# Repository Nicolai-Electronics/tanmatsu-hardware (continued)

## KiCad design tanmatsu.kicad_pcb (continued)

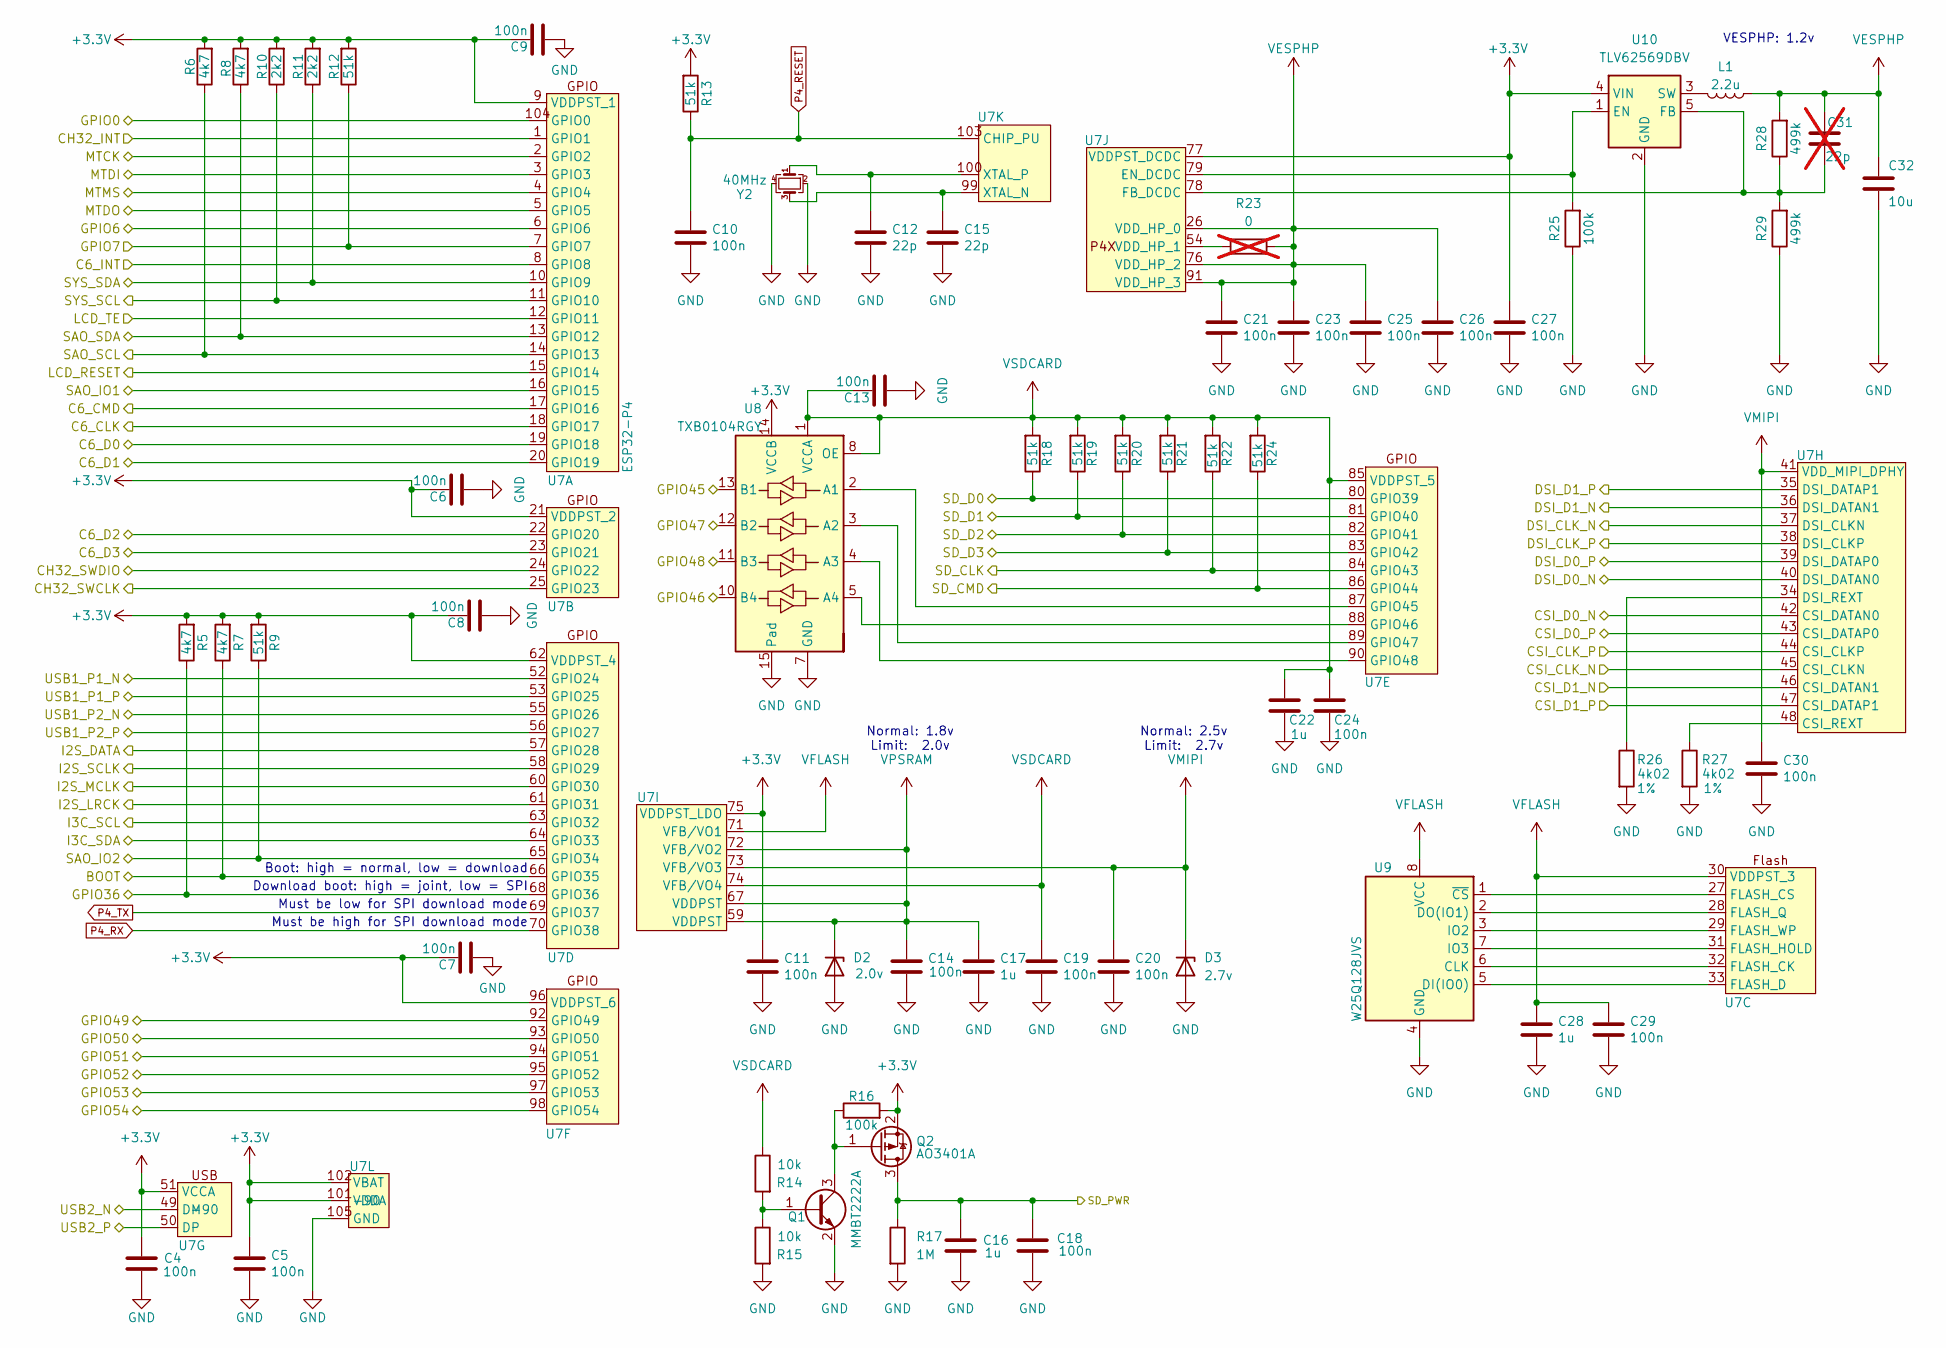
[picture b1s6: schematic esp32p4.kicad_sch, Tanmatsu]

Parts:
C4, C5, C6, C7, C8, C9, C10, C11, C13, C14, C18, C19, C20, C21, C23, C24, C25, C26, C27, C29, C30: 100n; C_0402_1005Metric; LCSC C307331
C12, C15: 22p; C_0402_1005Metric; LCSC C1555
C16, C17, C22, C28: 1u; C_0603_1608Metric; LCSC C5199872
C31: 22p; C_0402_1005Metric; LCSC C1555; not fitted
C32: 10u; C_0805_2012Metric; LCSC C3039694
D2: 2.0v; D_SOD-123; LCSC C438287
D3: 2.7v; D_SOD-323F; LCSC C550976
L1: 2.2u; Inductor_MSC20FC; LCSC C48945436
Q1: MMBT2222A; SOT-23; LCSC C8512
Q2: AO3401A; SOT-23; LCSC C15127
R5, R6, R7, R8: 4k7; R_0402_1005Metric; LCSC C25900
R9, R12, R13, R18, R19, R20, R21, R22, R24: 51k; R_0402_1005Metric; LCSC C25794
R10, R11: 2k2; R_0402_1005Metric; LCSC C25879
R14, R15: 10k; R_0402_1005Metric; LCSC C60490
R16, R25: 100k; R_0402_1005Metric; LCSC C25741
R17: 1M; R_0402_1005Metric; LCSC C26083
R23: 0; R_0402_1005Metric; LCSC C2906877; not fitted
R26, R27: 4k02; R_0402_1005Metric; LCSC C43251
R28, R29: 499k; R_0402_1005Metric; LCSC C137971
U7: ESP32-P4; QFN-104_EP_10x10_Pitch0.35mm-ESP32-P4; LCSC C22387510
U8: TXB0104RGY; Texas_S-PVQFN-N14; LCSC C400708
U9: W25Q128JVS; SOIC-8_5.23x5.23mm_P1.27mm; LCSC C97521
U10: TLV62569DBV; SOT-23-5; LCSC C141836
Y2: 40MHz; Crystal_SMD_3225-4Pin_3.2x2.5mm; LCSC C2901712

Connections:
+3.3V: C4.1, C5.1, C6.1, C7.1, C8.1, C9.1, C11.1, C27.1, Q2.2 (S), R5.2, R6.2, R7.2, R8.2, R9.2, R10.2, R11.2, R12.2, R13.2, R16.2, U7.9 (VDDPST_1), U7.21 (VDDPST_2), U7.51 (VCCA), U7.62 (VDDPST_4), U7.75 (VDDPST_LDO), U7.77 (VDDPST_DCDC), U7.96 (VDDPST_6), U7.101 (VDDA), U7.102 (VBAT), U8.14 (VCCB), U10.4 (VIN); also elsewhere on the board
/Application processor/C6_CLK: U7.18 (GPIO17); also elsewhere on the board
/Application processor/C6_CMD: U7.17 (GPIO16); also elsewhere on the board
/Application processor/C6_D0: U7.19 (GPIO18); also elsewhere on the board
/Application processor/C6_D1: U7.20 (GPIO19); also elsewhere on the board
/Application processor/C6_D2: U7.22 (GPIO20); also elsewhere on the board
/Application processor/C6_D3: U7.23 (GPIO21); also elsewhere on the board
/Application processor/C6_INT: U7.8 (GPIO8); also elsewhere on the board
/Application processor/CH32_INT: U7.1 (GPIO1); also elsewhere on the board
/Application processor/CH32_SWCLK: U7.25 (GPIO23); also elsewhere on the board
/Application processor/CH32_SWDIO: U7.24 (GPIO22); also elsewhere on the board
/Application processor/CSI_CLK_N: U7.45 (CSI_CLKN); also elsewhere on the board
/Application processor/CSI_CLK_P: U7.44 (CSI_CLKP); also elsewhere on the board
/Application processor/CSI_D0_N: U7.42 (CSI_DATAN0); also elsewhere on the board
/Application processor/CSI_D0_P: U7.43 (CSI_DATAP0); also elsewhere on the board
/Application processor/CSI_D1_N: U7.46 (CSI_DATAN1); also elsewhere on the board
/Application processor/CSI_D1_P: U7.47 (CSI_DATAP1); also elsewhere on the board
/Application processor/LCD_RESET: U7.15 (GPIO14); also elsewhere on the board
/Application processor/LCD_TE: U7.12 (GPIO11); also elsewhere on the board
/Application processor/SD_CLK: R22.1, U7.84 (GPIO43); also elsewhere on the board
/Application processor/SD_CMD: R24.1, U7.86 (GPIO44); also elsewhere on the board
/Application processor/SD_D0: R18.1, U7.80 (GPIO39); also elsewhere on the board
/Application processor/SD_D1: R19.1, U7.81 (GPIO40); also elsewhere on the board
/Application processor/SD_D2: R20.1, U7.82 (GPIO41); also elsewhere on the board
/Application processor/SD_D3: R21.1, U7.83 (GPIO42); also elsewhere on the board
/Application processor/SD_PWR: C16.1, C18.1, Q2.3 (D), R17.1; also elsewhere on the board
/Application processor/USB1_P1_N: U7.52 (GPIO24); also elsewhere on the board
/Application processor/USB1_P1_P: U7.53 (GPIO25); also elsewhere on the board
/Application processor/USB2_N: U7.49 (DM); also elsewhere on the board
/Application processor/USB2_P: U7.50 (DP); also elsewhere on the board
/DSI_CLK_N: U7.37 (DSI_CLKN); also elsewhere on the board
/DSI_CLK_P: U7.38 (DSI_CLKP); also elsewhere on the board
/DSI_D0_N: U7.40 (DSI_DATAN0); also elsewhere on the board
/DSI_D0_P: U7.39 (DSI_DATAP0); also elsewhere on the board
/DSI_D1_N: U7.36 (DSI_DATAN1); also elsewhere on the board
/DSI_D1_P: U7.35 (DSI_DATAP1); also elsewhere on the board
BOOT: R7.1, U7.66 (GPIO35); also elsewhere on the board
E0: R5.1, U7.68 (GPIO36); also elsewhere on the board
E1: U7.104 (GPIO0); also elsewhere on the board
E2: U7.6 (GPIO6); also elsewhere on the board
E3: U8.10 (B4); also elsewhere on the board
E4: U8.12 (B2); also elsewhere on the board
E5: U8.11 (B3); also elsewhere on the board
E6: U8.13 (B1); also elsewhere on the board
E7: R12.1, U7.7 (GPIO7); also elsewhere on the board
E8: U7.98 (GPIO54); also elsewhere on the board
E9: U7.92 (GPIO49); also elsewhere on the board
E10: U7.97 (GPIO53); also elsewhere on the board
E11: U7.95 (GPIO52); also elsewhere on the board
E12: U7.94 (GPIO51); also elsewhere on the board
E13: U7.93 (GPIO50); also elsewhere on the board
EXT_USB_N: U7.55 (GPIO26); also elsewhere on the board
EXT_USB_P: U7.56 (GPIO27); also elsewhere on the board
GND: C4.2, C5.2, C6.2, C7.2, C8.2, C9.2, C10.2, C11.2, C12.2, C13.2, C14.2, C15.2, C16.2, C17.2, C18.2, C19.2, C20.2, C21.2, C22.2, C23.2, C24.2, C25.2, C26.2, C27.2, C28.2, C29.2, C30.2, C32.2, D2.2 (A), D3.2 (A), Q1.2 (E), R15.2, R17.2, R25.1, R26.2, R27.2, R29.1, U7.105 (GND), U8.7 (GND), U8.15 (Pad), U9.4 (GND), U10.2 (GND), Y2.2, Y2.4; also elsewhere on the board
I2S_DATA: U7.57 (GPIO28); also elsewhere on the board
I2S_LRCK: U7.61 (GPIO31); also elsewhere on the board
I2S_MCLK: U7.60 (GPIO30); also elsewhere on the board
I2S_SCLK: U7.58 (GPIO29); also elsewhere on the board
I3C_SCL: U7.63 (GPIO32); also elsewhere on the board
I3C_SDA: U7.64 (GPIO33); also elsewhere on the board
INT_SCL: R10.1, U7.11 (GPIO10); also elsewhere on the board
INT_SDA: R11.1, U7.10 (GPIO9); also elsewhere on the board
MTCK: U7.2 (GPIO2); also elsewhere on the board
MTDI: U7.3 (GPIO3); also elsewhere on the board
MTDO: U7.5 (GPIO5); also elsewhere on the board
MTMS: U7.4 (GPIO4); also elsewhere on the board
unnamed: Q1.1 (B), R14.2, R15.1
unnamed: Q1.3 (C), Q2.1 (G), R16.1
unnamed: U7.32 (FLASH_CK), U9.6 (CLK)
unnamed: U7.27 (FLASH_CS), U9.1 (~CS)
unnamed: U7.33 (FLASH_D), U9.5 (DI(IO0))
unnamed: U7.31 (FLASH_HOLD), U9.7 (IO3)
unnamed: U7.28 (FLASH_Q), U9.2 (DO(IO1))
unnamed: U7.29 (FLASH_WP), U9.3 (IO2)
unnamed: U7.87 (GPIO45), U8.2 (A1)
unnamed: U7.88 (GPIO46), U8.5 (A4)
unnamed: U7.89 (GPIO47), U8.3 (A2)
unnamed: U7.90 (GPIO48), U8.4 (A3)
unnamed: R27.1, U7.48 (CSI_REXT)
unnamed: R26.1, U7.34 (DSI_REXT)
unnamed: R23.2, U7.54 (VDD_HP_1)
unnamed: C15.1, U7.99 (XTAL_N), Y2.3
unnamed: C12.1, U7.100 (XTAL_P), Y2.1
unnamed: R25.2, U7.79 (EN_DCDC), U10.1 (EN)
unnamed: C31.2, R28.1, R29.2, U7.78 (FB_DCDC), U10.5 (FB)
unnamed: L1.2, U10.3 (SW)
P4_RESET: C10.1, R13.1, U7.103 (CHIP_PU); also elsewhere on the board
P4_RX: U7.70 (GPIO38); also elsewhere on the board
P4_TX: U7.69 (GPIO37); also elsewhere on the board
SAO_IO1: U7.16 (GPIO15); also elsewhere on the board
SAO_IO2: R9.1, U7.65 (GPIO34); also elsewhere on the board
SAO_SCL: R6.1, U7.14 (GPIO13); also elsewhere on the board
SAO_SDA: R8.1, U7.13 (GPIO12); also elsewhere on the board
VESPHP: C21.1, C23.1, C25.1, C26.1, C31.1, C32.1, L1.1, R23.1, R28.2, U7.26 (VDD_HP_0), U7.76 (VDD_HP_2), U7.91 (VDD_HP_3)
VFLASH: C28.1, C29.1, U7.30 (VDDPST_3), U7.71 (VFB/VO1), U9.8 (VCC)
VMIPI: C20.1, C30.1, D3.1 (K), U7.41 (VDD_MIPI_DPHY), U7.73 (VFB/VO3)
VPSRAM: C14.1, C17.1, D2.1 (K), U7.59 (VDDPST), U7.67 (VDDPST), U7.72 (VFB/VO2)
VSDCARD: C13.1, C19.1, C22.1, C24.1, R14.1, R18.2, R19.2, R20.2, R21.2, R22.2, R24.2, U7.74 (VFB/VO4), U7.85 (VDDPST_5), U8.1 (VCCA), U8.8 (OE)

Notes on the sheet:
Normal: 1.8v Limit: 2.0v
Boot: high = normal, low = download
Must be high for SPI download mode
Normal: 2.5v Limit: 2.7v
Must be low for SPI download mode
Download boot: high = joint, low = SPI
VESPHP: 1.2v

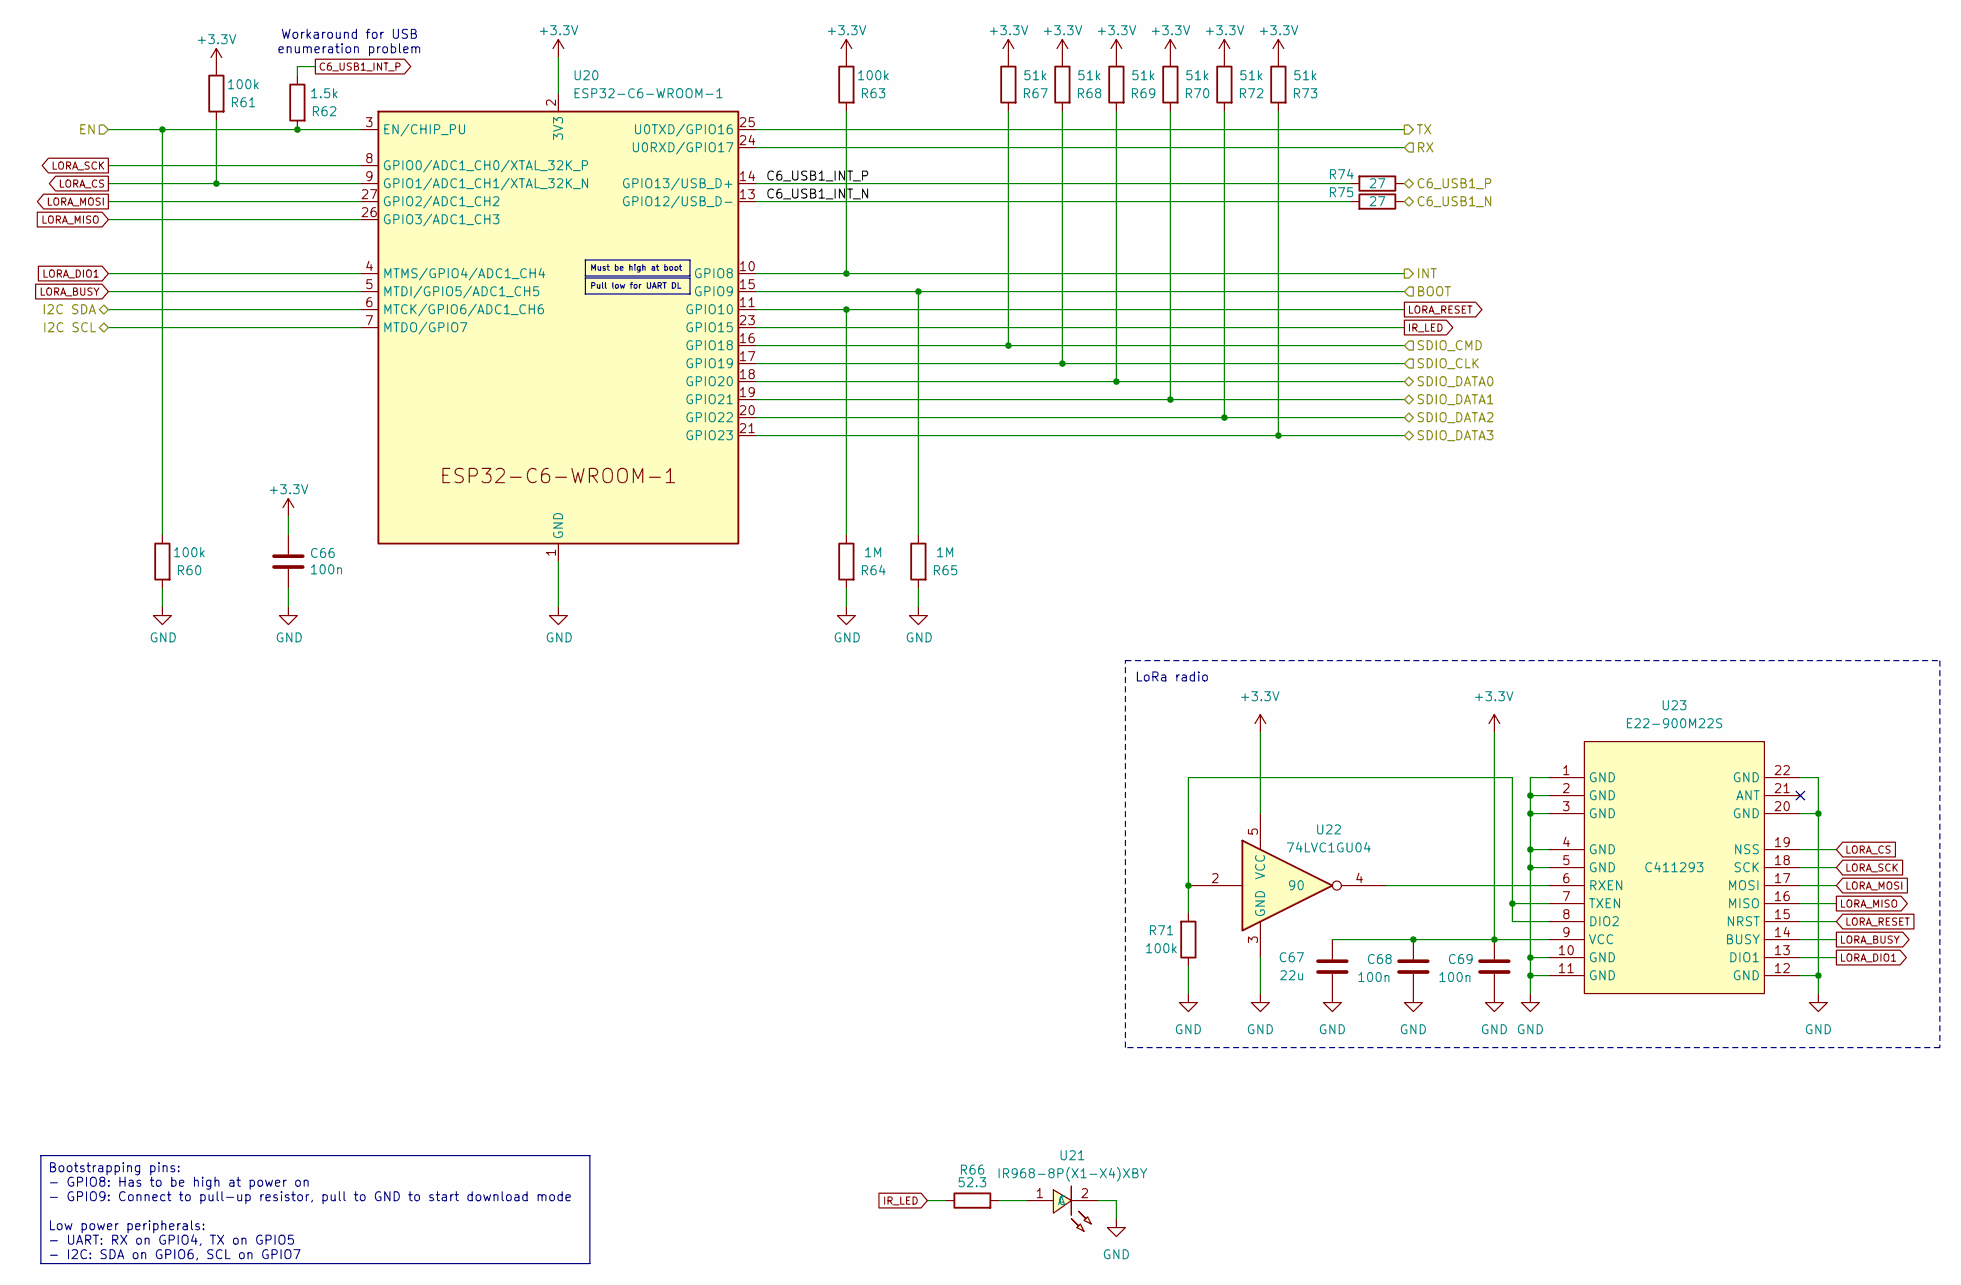
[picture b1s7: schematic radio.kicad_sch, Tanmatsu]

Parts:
C66, C68, C69: 100n; C_0402_1005Metric; LCSC C307331
C67: 22u; C_0805_2012Metric; LCSC C602037
R60, R61, R63, R71: 100k; R_0402_1005Metric; LCSC C25741
R62: 1.5k; R_0402_1005Metric; LCSC C25867
R64, R65: 1M; R_0402_1005Metric; LCSC C26083
R66: 52.3; R_0402_1005Metric; LCSC C114978
R67, R68, R69, R70, R72, R73: 51k; R_0402_1005Metric; LCSC C25794
R74, R75: 27; R_0402_1005Metric; LCSC C25100
U20: ESP32-C6-WROOM-1; LCSC C5366877
U21: IR968-8P(X1-X4)XBY; LED-TH_L3.0-W2.9-P2.54-FD; LCSC C47416529
U22: 74LVC1GU04; SOT-353_SC-70-5; LCSC C485082
U23: E22-900M22S; WIRELM-SMD_E22-900M22S; LCSC C411293

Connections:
+3.3V: C66.1, C67.1, C68.1, C69.1, R61.1, R63.1, R67.1, R68.1, R69.1, R70.1, R72.1, R73.1, U20.2 (3V3), U22.5 (VCC), U23.9 (VCC); also elsewhere on the board
/Application processor/C6_CLK: R68.2, U20.17 (GPIO19); also elsewhere on the board
/Application processor/C6_CMD: R67.2, U20.16 (GPIO18); also elsewhere on the board
/Application processor/C6_D0: R69.2, U20.18 (GPIO20); also elsewhere on the board
/Application processor/C6_D1: R70.2, U20.19 (GPIO21); also elsewhere on the board
/Application processor/C6_D2: R72.2, U20.20 (GPIO22); also elsewhere on the board
/Application processor/C6_D3: R73.2, U20.21 (GPIO23); also elsewhere on the board
/Application processor/C6_INT: R63.2, U20.10 (GPIO8); also elsewhere on the board
/Coprocessor/RADIO_BOOT: R65.1, U20.15 (GPIO9); also elsewhere on the board
/Radio/C6_USB1_INT_N: R75.2, U20.13 (GPIO12/USB_D-)
/Radio/C6_USB1_N: R75.1; also elsewhere on the board
/Radio/C6_USB1_P: R74.1; also elsewhere on the board
/Radio/TX: U20.25 (U0TXD/GPIO16); also elsewhere on the board
C6_USB1_INT_P: R62.1, R74.2, U20.14 (GPIO13/USB_D+)
CAM_IO0: R60.1, R62.2, U20.3 (EN/CHIP_PU); also elsewhere on the board
E10: U20.24 (U0RXD/GPIO17); also elsewhere on the board
GND: C66.2, C67.2, C68.2, C69.2, R60.2, R64.2, R65.2, R71.1, U20.1 (GND), U20.12 (GPIO11), U20.28 (GND), U20.29 (GND), U21.2 (C), U22.3 (GND), U23.1 (GND), U23.2 (GND), U23.3 (GND), U23.4 (GND), U23.5 (GND), U23.10 (GND), U23.11 (GND), U23.12 (GND), U23.20 (GND), U23.22 (GND); also elsewhere on the board
INT_SCL: U20.7 (MTDO/GPIO7); also elsewhere on the board
INT_SDA: U20.6 (MTCK/GPIO6/ADC1_CH6); also elsewhere on the board
IR_LED: R66.1, U20.23 (GPIO15)
LORA_BUSY: U20.5 (MTDI/GPIO5/ADC1_CH5), U23.14 (BUSY)
LORA_CS: R61.2, U20.9 (GPIO1/ADC1_CH1/XTAL_32K_N), U23.19 (NSS)
LORA_DIO1: U20.4 (MTMS/GPIO4/ADC1_CH4), U23.13 (DIO1)
LORA_MISO: U20.26 (GPIO3/ADC1_CH3), U23.16 (MISO)
LORA_MOSI: U20.27 (GPIO2/ADC1_CH2), U23.17 (MOSI)
LORA_RESET: R64.1, U20.11 (GPIO10), U23.15 (NRST)
LORA_SCK: U20.8 (GPIO0/ADC1_CH0/XTAL_32K_P), U23.18 (SCK)
unnamed: R66.2, U21.1 (A)
unnamed: R71.2, U22.2, U23.7 (TXEN), U23.8 (DIO2)
unnamed: U22.4, U23.6 (RXEN)

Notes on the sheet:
LoRa radio
Workaround for USB enumeration problem
Pull low for UART DL
Must be high at boot
Bootstrapping pins: - GPIO8: Has to be high at power on - GPIO9: Connect to pull-up resistor, pull to GND to start download mode Low power peripherals: - UART: RX on GPIO4, TX on GPIO5 - I2C: SDA on GPIO6, SCL on GPIO7

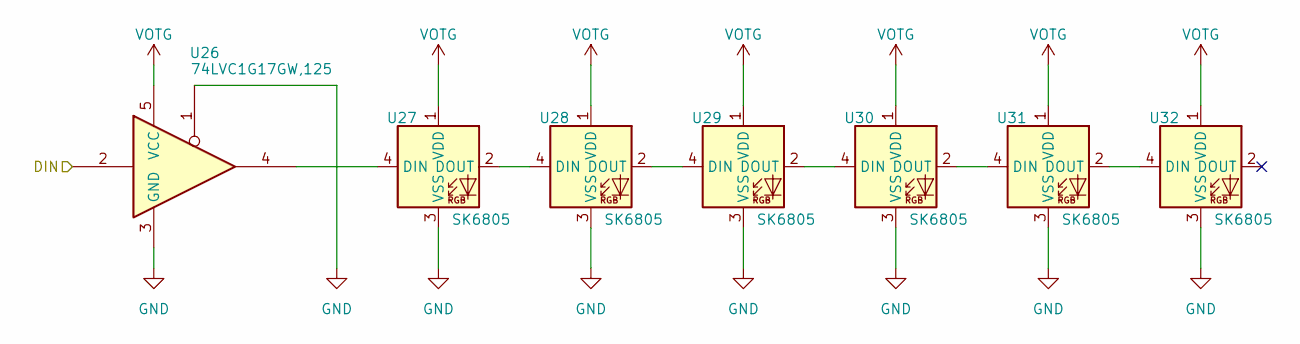
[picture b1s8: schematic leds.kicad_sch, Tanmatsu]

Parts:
U26: 74LVC1G17GW,125; SOT-353_SC-70-5; LCSC C426705
U27, U28, U29, U30, U31, U32: SK6805; SK6805-EC20; LCSC C2890036

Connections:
/Coprocessor/LED_DATA: U26.2; also elsewhere on the board
GND: U26.1, U26.3 (GND), U27.3 (VSS), U28.3 (VSS), U29.3 (VSS), U30.3 (VSS), U31.3 (VSS), U32.3 (VSS); also elsewhere on the board
unnamed: U26.4, U27.4 (DIN)
unnamed: U27.2 (DOUT), U28.4 (DIN)
unnamed: U28.2 (DOUT), U29.4 (DIN)
unnamed: U29.2 (DOUT), U30.4 (DIN)
unnamed: U30.2 (DOUT), U31.4 (DIN)
unnamed: U31.2 (DOUT), U32.4 (DIN)
VOTG: U26.5 (VCC), U27.1 (VDD), U28.1 (VDD), U29.1 (VDD), U30.1 (VDD), U31.1 (VDD), U32.1 (VDD); also elsewhere on the board

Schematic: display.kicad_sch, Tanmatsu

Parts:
C83, C84, C85, C86: 10n; C_0402_1005Metric; LCSC C15195
CN1: Display; tanmatsu_display; LCSC C3036280
R86: 51k; R_0402_1005Metric; LCSC C25794
R87: 100k; R_0402_1005Metric; LCSC C25741

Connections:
+3.3V: C83.1, C84.1, C85.1, C86.1, CN1.23 (VCI), CN1.24 (IOVCC), R86.1; also elsewhere on the board
+BL-LCD: CN1.2 (LCM_LEDA); also elsewhere on the board
-BL-LCD: CN1.1 (LCM_LEDK); also elsewhere on the board
/Application processor/LCD_RESET: CN1.21 (LCM_RST), R86.2; also elsewhere on the board
/Application processor/LCD_TE: CN1.20 (DSI_TE), R87.1; also elsewhere on the board
/DSI_CLK_N: CN1.8 (TCN); also elsewhere on the board
/DSI_CLK_P: CN1.7 (TCP); also elsewhere on the board
/DSI_D0_N: CN1.5 (TDN0); also elsewhere on the board
/DSI_D0_P: CN1.4 (TDP0); also elsewhere on the board
/DSI_D1_N: CN1.11 (TDN1); also elsewhere on the board
/DSI_D1_P: CN1.10 (TDP1); also elsewhere on the board
GND: C83.2, C84.2, C85.2, C86.2, CN1.3 (GND), CN1.6 (GND), CN1.9 (GND), CN1.12 (GND), CN1.13 (TP-SCL), CN1.14 (TP-SDA), CN1.15 (TP-RST), CN1.16 (TP-INT), CN1.17 (TP-VDD), CN1.18 (GND), CN1.19 (GND), CN1.22 (GND), CN1.25, CN1.26, R87.2; also elsewhere on the board

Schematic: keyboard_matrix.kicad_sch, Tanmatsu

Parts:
D4, D5, D6, D7, D14, D15, D16, D17: LTW-010DCG-SR-G; LCSC C5175309
D8, D9, D10, D11, D12, D13, D18, D19, D20, D21, D22, D23, D24, D25, D26, D27, D28, D29, D30, D31, D32, D33, D34, D35, D36, D37, D38, D39, D40, D41, D42, D43, D44, D45, D46, D47, D48, D49, D50, D51, D52, D53, D54, D55, D56, D57, D58, D59, D60, D61, D62, D63, D64, D65, D66, D67, D68, D69, D70, D71, D72, D73, D74, D75, D76, D77, D78, D79, D80, D81, D82, D83: 1N4148WS; D_SOD-323; LCSC C2843305
Q3: AP2302B; SOT-23; LCSC C406812
R37: 100k; R_0402_1005Metric; LCSC C25741
R38: 4k7; R_0402_1005Metric; LCSC C25900
R39, R40, R41, R42, R43, R44, R45, R46: 10k; R_0402_1005Metric; LCSC C60490
U13: Keyboard; keyboard_arturo182

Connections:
+BL-KB: D4.2 (A), D14.2 (A); also elsewhere on the board
-BL-KB: D7.1 (K), D17.1 (K); also elsewhere on the board
/Coprocessor/Keyboard/EXT: R37.2, R38.1; also elsewhere on the board
GND: R37.1, R39.2, R40.2, R41.2, R42.2, R43.2, R44.2, R45.2, R46.2; also elsewhere on the board
KB_COL0: D8.1 (K), D10.1 (K), D12.1 (K), D36.1 (K), D38.1 (K), D56.1 (K), D60.1 (K), D62.1 (K), D64.1 (K), R39.1; also elsewhere on the board
KB_COL1: D18.1 (K), D20.1 (K), D22.1 (K), D40.1 (K), D42.1 (K), D57.1 (K), D66.1 (K), D68.1 (K), D70.1 (K), R40.1; also elsewhere on the board
KB_COL2: D24.1 (K), D26.1 (K), D28.1 (K), D45.1 (K), D47.1 (K), D58.1 (K), D72.1 (K), D74.1 (K), D76.1 (K), R41.1; also elsewhere on the board
KB_COL3: D30.1 (K), D32.1 (K), D34.1 (K), D50.1 (K), D52.1 (K), D59.1 (K), D78.1 (K), D80.1 (K), D82.1 (K), R42.1; also elsewhere on the board
KB_COL4: D9.1 (K), D11.1 (K), D13.1 (K), D37.1 (K), D39.1 (K), D44.1 (K), D61.1 (K), D63.1 (K), D65.1 (K), R43.1; also elsewhere on the board
KB_COL5: D19.1 (K), D21.1 (K), D23.1 (K), D41.1 (K), D43.1 (K), D49.1 (K), D67.1 (K), D69.1 (K), D71.1 (K), R44.1; also elsewhere on the board
KB_COL6: D25.1 (K), D27.1 (K), D29.1 (K), D46.1 (K), D48.1 (K), D54.1 (K), D73.1 (K), D75.1 (K), D77.1 (K), R45.1; also elsewhere on the board
KB_COL7: D31.1 (K), D33.1 (K), D35.1 (K), D51.1 (K), D53.1 (K), D55.1 (K), D79.1 (K), D81.1 (K), D83.1 (K), R46.1; also elsewhere on the board
KB_ROW0: U13.1 (ESC), U13.3 (F1), U13.5 (F2), U13.7 (F3), U13.17 (`), U13.19 (1), U13.21 (2), U13.23 (3); also elsewhere on the board
KB_ROW1: U13.43 (TAB), U13.45 (Q), U13.47 (W), U13.49 (E), U13.69 (FN), U13.71 (A), U13.73 (S), U13.75 (D); also elsewhere on the board
KB_ROW2: U13.95 (SHL), U13.97 (Z), U13.99 (X), U13.101 (C), U13.121 (CTRL), U13.123 (MT), U13.125 (ALT), U13.127 (\); also elsewhere on the board
KB_ROW3: U13.25 (4), U13.27 (5), U13.29 (6), U13.31 (7), U13.51 (R), U13.53 (T), U13.55 (Y), U13.57 (U); also elsewhere on the board
KB_ROW4: U13.77 (F), U13.79 (G), U13.81 (H), U13.83 (J), U13.103 (V), U13.105 (B), U13.107 (N), U13.109 (M); also elsewhere on the board
KB_ROW5: U13.9 (F4), U13.11 (F5), U13.13 (F6), U13.15 (BS), U13.35 (9), U13.37 (0), U13.39 (-), U13.41 (=); also elsewhere on the board
KB_ROW6: U13.61 (O), U13.63, U13.65 ([), U13.67 (]), U13.87 (L), U13.89 (;), U13.91 ('), U13.93 (RET); also elsewhere on the board
KB_ROW7: U13.113 (.), U13.115 (/), U13.117 (/\), U13.119 (SHR), U13.135 (AGR), U13.137 (<), U13.139 (\/), U13.141 (>); also elsewhere on the board
KB_ROW8: Q3.3 (D), U13.33 (8), U13.59 (I), U13.85 (K), U13.111 (,), U13.129 (SP), U13.131 (SP), U13.133 (SP); also elsewhere on the board
unnamed: D4.1 (K), D5.2 (A)
unnamed: D5.1 (K), D6.2 (A)
unnamed: D6.1 (K), D7.2 (A)
unnamed: D8.2 (A), U13.2
unnamed: D9.2 (A), U13.18
unnamed: D10.2 (A), U13.44
unnamed: D11.2 (A), U13.70
unnamed: D12.2 (A), U13.96
unnamed: D13.2 (A), U13.122
unnamed: D14.1 (K), D15.2 (A)
unnamed: D15.1 (K), D16.2 (A)
unnamed: D16.1 (K), D17.2 (A)
unnamed: D18.2 (A), U13.4
unnamed: D19.2 (A), U13.20
unnamed: D20.2 (A), U13.46
unnamed: D21.2 (A), U13.72
unnamed: D22.2 (A), U13.98
unnamed: D23.2 (A), U13.124
unnamed: D24.2 (A), U13.6
unnamed: D25.2 (A), U13.22
unnamed: D26.2 (A), U13.48
unnamed: D27.2 (A), U13.74
unnamed: D28.2 (A), U13.100
unnamed: D29.2 (A), U13.126
unnamed: D30.2 (A), U13.8
unnamed: D31.2 (A), U13.24
unnamed: D32.2 (A), U13.50
unnamed: D33.2 (A), U13.76
unnamed: D34.2 (A), U13.102
unnamed: D35.2 (A), U13.128
unnamed: D36.2 (A), U13.26
unnamed: D37.2 (A), U13.52
unnamed: D38.2 (A), U13.78
unnamed: D39.2 (A), U13.104
unnamed: D40.2 (A), U13.28
unnamed: D41.2 (A), U13.54
unnamed: D42.2 (A), U13.80
unnamed: D43.2 (A), U13.106
unnamed: D44.2 (A), U13.130
unnamed: D45.2 (A), U13.30
unnamed: D46.2 (A), U13.56
unnamed: D47.2 (A), U13.82
unnamed: D48.2 (A), U13.108
unnamed: D49.2 (A), U13.132
unnamed: D50.2 (A), U13.32
unnamed: D51.2 (A), U13.58
unnamed: D52.2 (A), U13.84
unnamed: D53.2 (A), U13.110
unnamed: D54.2 (A), U13.134
unnamed: D55.2 (A), Q3.2 (S)
unnamed: D56.2 (A), U13.34
unnamed: D57.2 (A), U13.60
unnamed: D58.2 (A), U13.86
unnamed: D59.2 (A), U13.112
unnamed: D60.2 (A), U13.10
unnamed: D61.2 (A), U13.36
unnamed: D62.2 (A), U13.62
unnamed: D63.2 (A), U13.88
unnamed: D64.2 (A), U13.114
unnamed: D65.2 (A), U13.136
unnamed: D66.2 (A), U13.12
unnamed: D67.2 (A), U13.38
unnamed: D68.2 (A), U13.64
unnamed: D69.2 (A), U13.90
unnamed: D70.2 (A), U13.116
unnamed: D71.2 (A), U13.138
unnamed: D72.2 (A), U13.14
unnamed: D73.2 (A), U13.40
unnamed: D74.2 (A), U13.66
unnamed: D75.2 (A), U13.92
unnamed: D76.2 (A), U13.118
unnamed: D77.2 (A), U13.140
unnamed: D78.2 (A), U13.16
unnamed: D79.2 (A), U13.42
unnamed: D80.2 (A), U13.68
unnamed: D81.2 (A), U13.94
unnamed: D82.2 (A), U13.120
unnamed: D83.2 (A), U13.142
unnamed: Q3.1 (G), R38.2

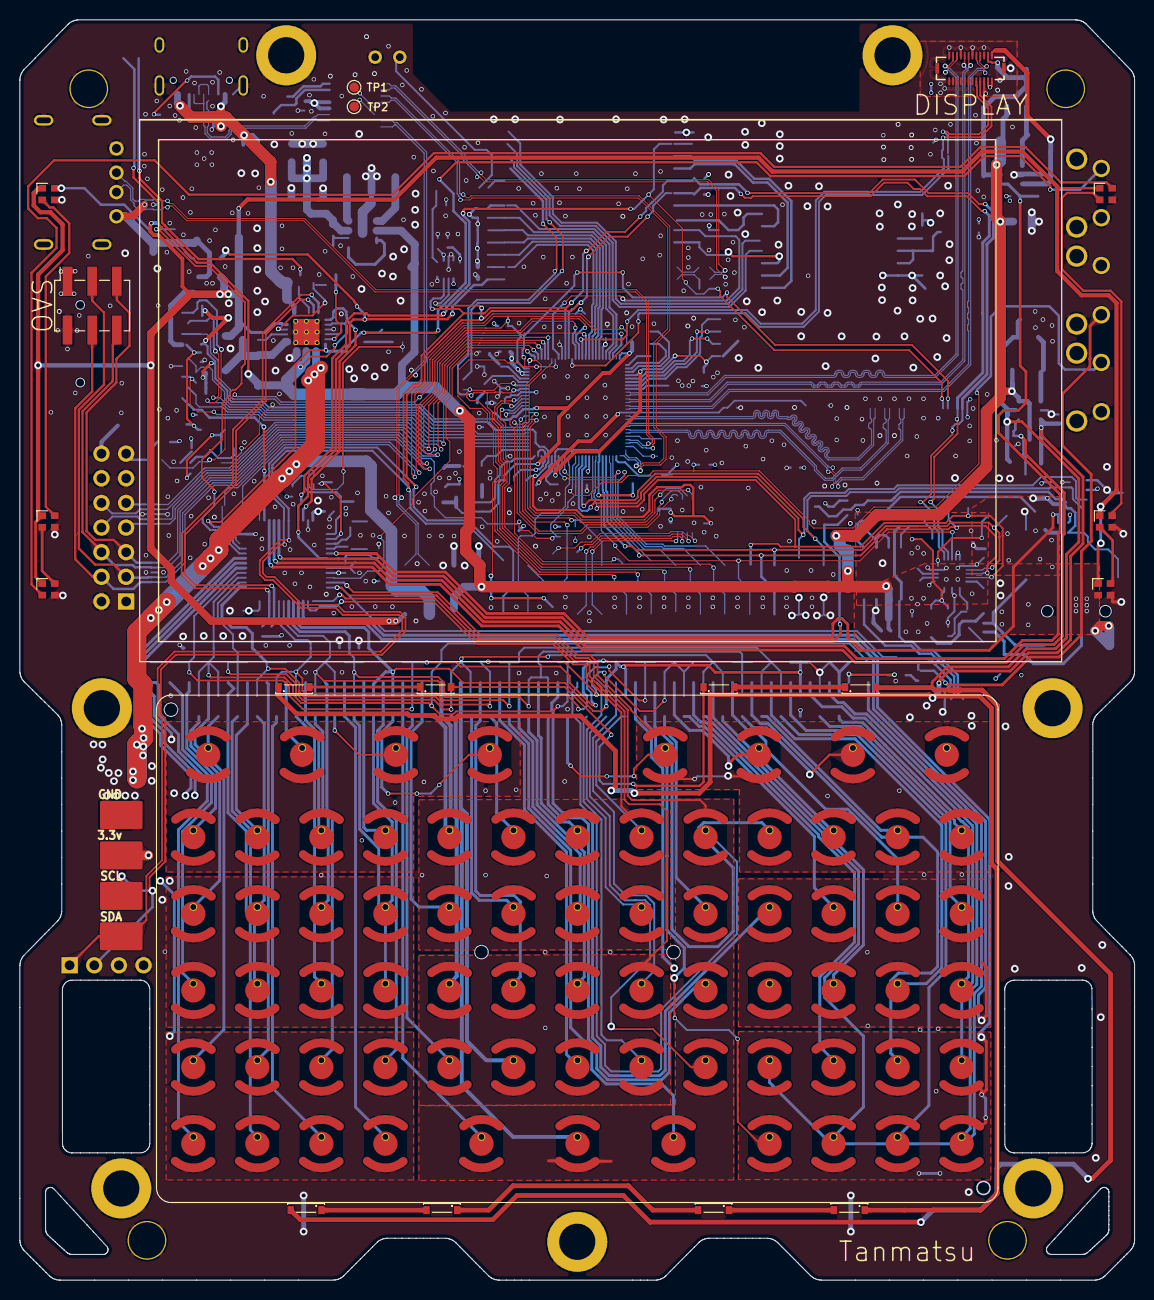
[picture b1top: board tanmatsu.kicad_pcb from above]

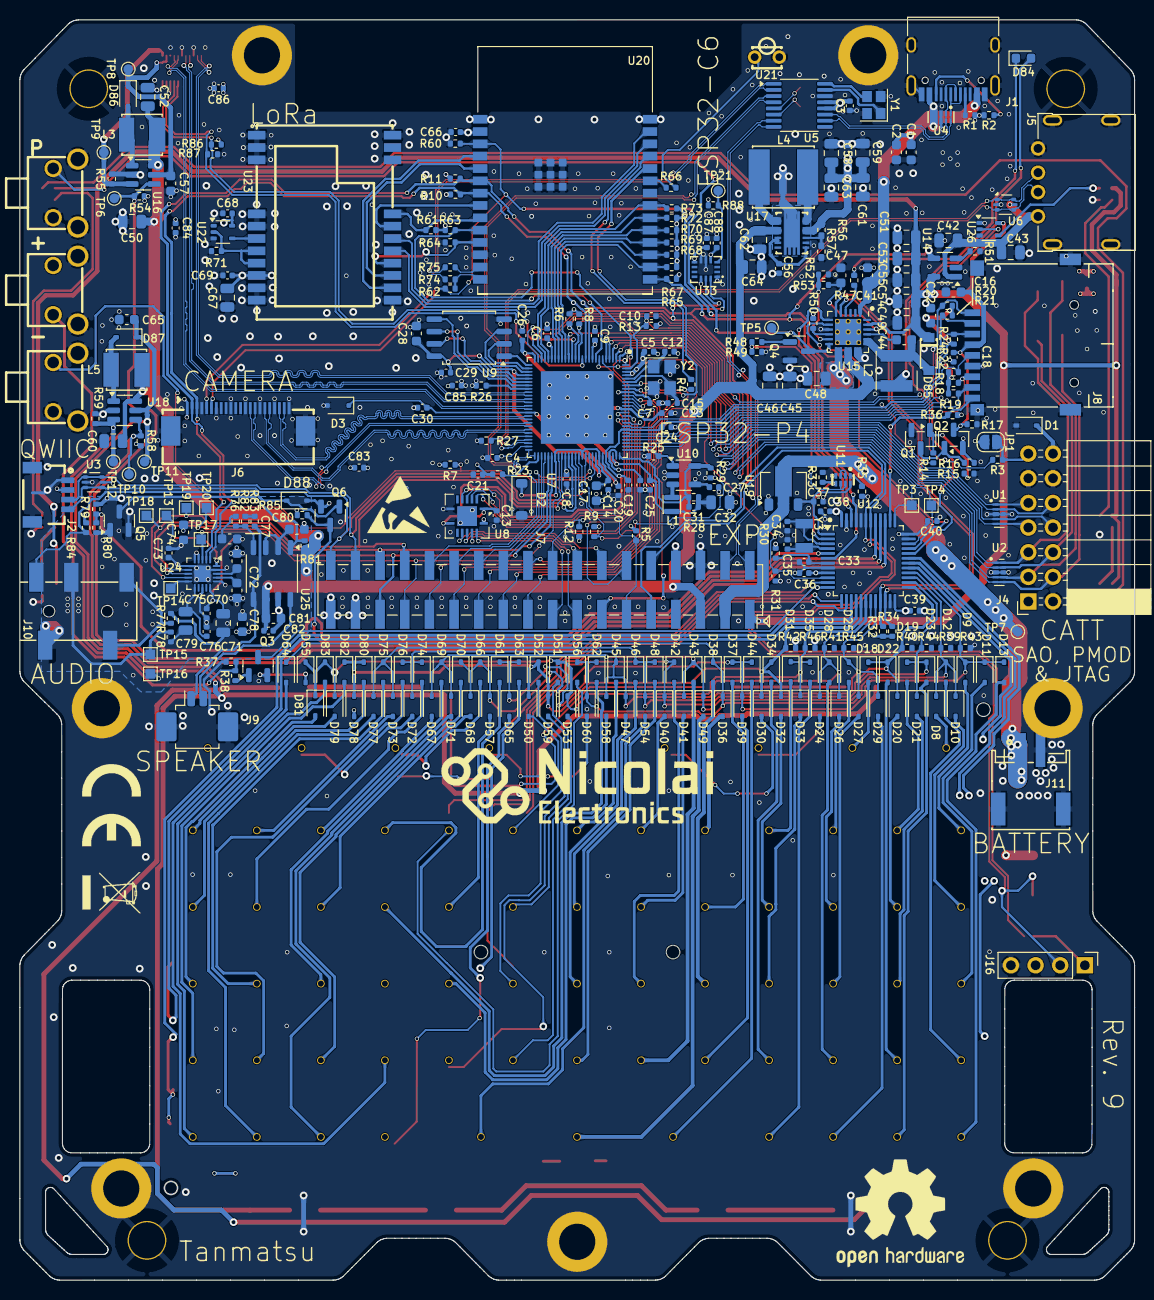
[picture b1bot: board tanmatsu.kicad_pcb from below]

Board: 4 copper layers, 114.9 x 129.9 mm, 372 parts (341 on the bottom side), 294 nets.

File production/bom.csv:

Designator,Footprint,Quantity,Value,LCSC Part #
"C1, C16, C17, C2, C22, C28, C41, C57, C65, C70, C71, C72, C74, C80, C81",0603,15,1u,C5199872
"C10, C11, C13, C14, C18, C19, C20, C21, C23, C24, C25, C26, C27, C29, C3, C30, C33, C36, C37, C38, C39, C4, C40, C5, C56, C6, C66, C68, C69, C7, C73, C8, C82, C87, C88, C9",0402,36,100n,C307331
"C12, C15, C34, C35, C75, C76",0402,6,22p,C1555
"C32, C42, C43, C45, C46, C48, C49, C50, C51, C52, C53, C54, C55, C60, C62, C64",0805,16,10u,C3039694
C44,0603,1,47n,C469624
C47,0603,1,4u7,C69335
"C58, C59, C61, C63, C67, C78, C79",0805,7,22u,C602037
C77,0603,1,0.39u,C1623
"C83, C84, C85, C86",0402,4,10n,C15195
CN1,tanmatsu_display,1,Display,C3036280
"D1, D88",D_SOD-323,2,ESD prot.,C22363742
"D10, D11, D12, D13, D18, D19, D20, D21, D22, D23, D24, D25, D26, D27, D28, D29, D30, D31, D32, D33, D34, D35, D36, D37, D38, D39, D40, D41, D42, D43, D44, D45, D46, D47, D48, D49, D50, D51, D52, D53, D54, D55, D56, D57, D58, D59, D60, D61, D62, D63, D64, D65, D66, D67, D68, D69, D70, D71, D72, D73, D74, D75, D76, D77, D78, D79, D8, D80, D81, D82, D83, D9",D_SOD-323,72,1N4148WS,C2843305
"D14, D15, D16, D17, D4, D5, D6, D7",LTW-010DCG-SR-G,8,LTW-010DCG-SR-G,C5175309
D2,D_SOD-123,1,2.0v,C438287
D3,D_SOD-323F,1,2.7v,C550976
D84,0603,1,LED,C7496820
D85,SOD-123_L2.8-W1.8-LS3.7-RD,1,SMD24PL-TP,C151787
"D86, D87",D_SOD-323,2,1N5819WS,C369937
"H1, H10, H11, H2, H3, H4, H5, H6, H7, H8, H9",SMTSO2030CTJ,11,Mounting hole,C2915626
J1,USB_C_Receptacle_HRO_TYPE-C-31-M-12,1,USB device,C165948
J10,PJ-327ST-SMT,1,Headphone,C319103
J11,CONN-SMD_PH-2AWB,1,Battery,C20598817
J16,PinHeader_1x04_P2.54mm_Vertical,1,Sensor,C2691448
J2,1X04_1MM_RA_GND,1,Expansion I3C,C7433425
J4,PinSocket_2x07_P2.54mm_Horizontal,1,External Add-On (SAO / PMOD),C2936004
J5,USB-A-TH_JTJ-USB-A-F-10.0-010,1,USB host,C42576
J6,FPC-SMD_XUNPU_FPC-0.5FX-22PWBH20,1,CAMERA,C3446014
J7,PinSocket_2x18_P2.54mm_Vertical_SMD,1,Internal Add-On,C3975163
J8,SD_Card-micro_socket_A,1,Micro_SD_Card,C7529389
J9,Molex_PicoBlade_53261-0271_1x02-1MP_P1.25mm_Horizontal,1,Speaker,C3029359
L1,Inductor_MSC20FC,1,2.2u,C48945436
L2,L_Wurth_WE-LQSH-4020,1,YHNR4020-2R2M,C2926400
"L3, L5",IND-SMD_L4.0-W4.0,2,6.8uH,C520306
L4,IND-SMD_L6.0-W6.0,1,CMLW6028S1R5MST,C431354
Q1,SOT-23,1,MMBT2222A,C8512
Q2,SOT-23,1,AO3401A,C15127
"Q3, Q4, Q5, Q6",SOT-23,4,AP2302B,C406812
"R1, R2",0402,2,5k1,C25905
"R10, R11, R4",0402,3,2k2,C25879
"R12, R13, R18, R19, R20, R21, R22, R24, R67, R68, R69, R70, R72, R73, R86, R9",0402,16,51k,C25794
"R14, R15, R30, R31, R35, R39, R40, R41, R42, R43, R44, R45, R46, R52, R53, R76, R81, R82, R83",0402,19,10k,C60490
"R16, R25, R36, R37, R49, R54, R58, R60, R61, R63, R71, R79, R84, R85, R87",0402,15,100k,C25741
"R17, R33, R56, R64, R65",0402,5,1M,C26083
"R26, R27",0402,2,4k02,C43251
"R28, R29",0402,2,499k,C137971
"R3, R47",0402,2,1k,C11702
"R32, R34, R38, R48, R5, R6, R7, R8, R80, R88",0402,10,4k7,C25900
R50,0402,1,261,C7467416
R51,0402,1,6.8k,C25917
R55,0402,1,10,C25077
R57,0402,1,180k,C2909325
R59,0402,1,4R7,C25121
R62,0402,1,1.5k,C25867
R66,0402,1,52.3,C114978
"R74, R75",0402,2,27,C25100
"R77, R78",0402,2,33,C25105
SW1,KEY-TH_TC-1101V-C-A-W,1,Boot,C318992
SW2,KEY-TH_TC-1101V-C-A-W,1,User,C318992
SW3,KEY-TH_TC-1101V-C-A-W,1,Power,C318992
"U1, U2",Diodes_UDFN-10_1.0x2.5mm_P0.5mm,2,ESD,C5180236
U10,SOT-23-5,1,TLV62569DBV,C141836
U11,X2-DFN2010-8_L2.0-W1.0-P0.50-BL,1,74LVC2G02HD4-7,C842640
U12,LQFP-48_7x7mm_P0.5mm,1,CH32V203C8T6,C3001172
U14,SOT-23-5,1,SY6280AAC,C55136
U15,Texas_S-PWQFN-N24_EP2.7x2.7mm_ThermalVias,1,BQ25895RTW,C80200
"U16, U18",SOT-23-6,2,AP3032KTR,C264086
U17,VSON-14_L4.0-W3.0-P0.50-BL-EP_TI_DSJ,1,TPS63020DSJR,C15483
U19,SOT-89-3,1,LR8341A-M25,C5205210
U20,ESP32-C6-WROOM-1,1,ESP32-C6-WROOM-1,C5366877
U21,LED-TH_L3.0-W2.9-P2.54-FD,1,IR968-8P(X1-X4)XBY,C47416529
U22,SOT-353_SC-70-5,1,74LVC1GU04,C485082
U23,WIRELM-SMD_E22-900M22S,1,E22-900M22S,C411293
U24,VQFN-20-1EP_3x3mm_P0.4mm_EP1.7x1.7mm,1,ES8156,C2887138
U25,SSOP-8_3.9x5.05mm_P1.27mm,1,FM8002A,C94625
U26,SOT-353_SC-70-5,1,"74LVC1G17GW,125",C426705
"U27, U28, U29, U30, U31, U32",SK6805-EC20,6,SK6805,C2890036
"U3, U6",SOT-666,2,USBLC6-2P6,C2827693
U33,LGA-14_L3.0-W2.5-P0.50-BR,1,BMI270,C2836813
U4,USON-10_L2.5-W1.0-P0.50-BL,1,TPD4E05U06DQAR,C138714
U5,QSOP-16_3.9x4.9mm_P0.635mm,1,CH334R,C4154405
U7,QFN-104_EP_10x10_Pitch0.35mm-ESP32-P4,1,ESP32-P4,C22387510
U8,Texas_S-PVQFN-N14,1,TXB0104RGY,C400708
U9,SOIC-8_5.23x5.23mm_P1.27mm,1,W25Q128JVS,C97521
Y1,Crystal_SMD_2520-4Pin_2.5x2.0mm,1,12MHz,C284156
Y2,Crystal_SMD_3225-4Pin_3.2x2.5mm,1,40MHz,C2901712
Y3,Crystal_SMD_3215-2Pin_3.2x1.5mm,1,32.768KHz,C95361
